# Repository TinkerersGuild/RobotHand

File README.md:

# RobotHand
http://tinker.eccentrify.com/guild/projects/robot-hand/

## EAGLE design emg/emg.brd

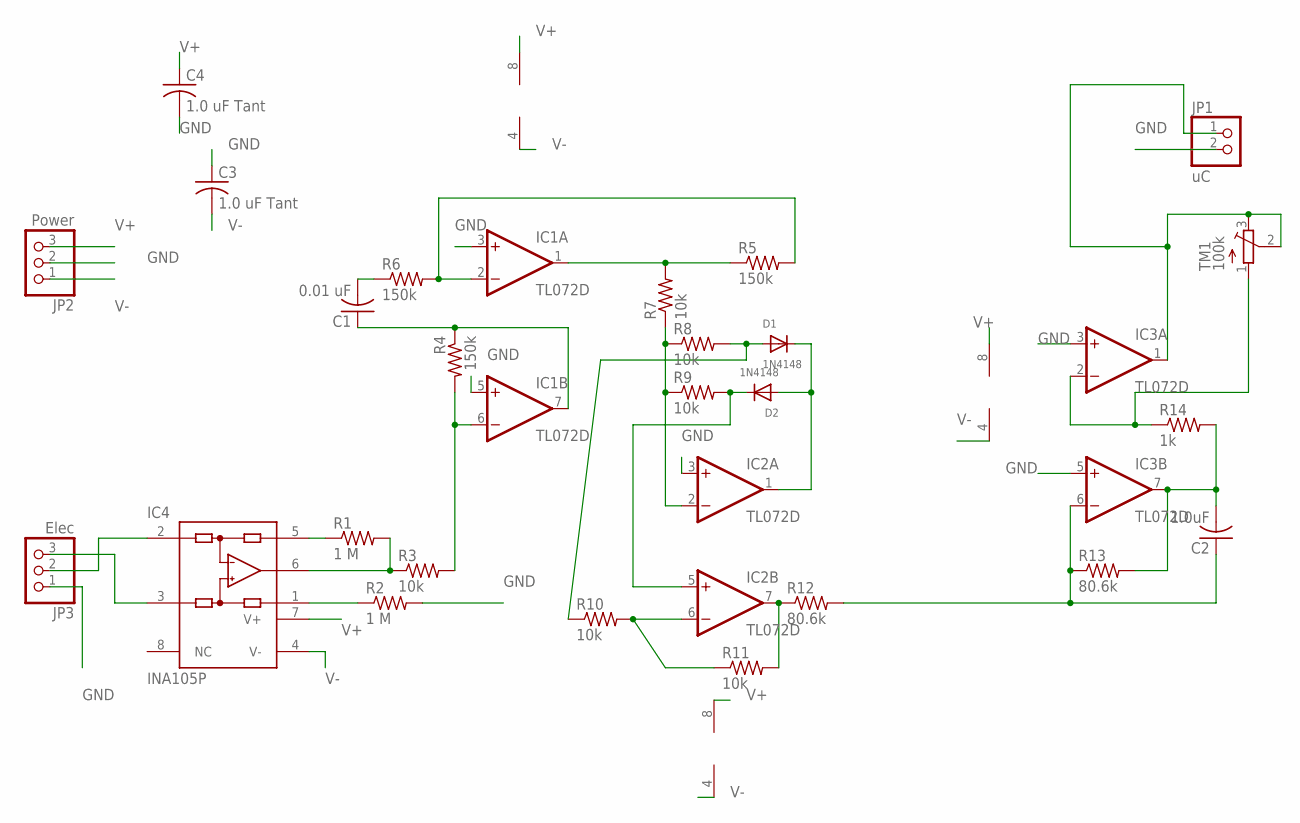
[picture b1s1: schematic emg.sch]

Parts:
C1: 0.01 uF; C0603
C2: 1.0uF; C0603
C3, C4: 1.0 uF Tant; C0805
D1, D2: 1N4148; DO-1N4148
IC1, IC2, IC3: TL072D; SO08
IC4: INA105P; DIL08
JP1: uC; 1X02
JP2: Power; 1X03
JP3: Elec; 1X03
R1, R2: 1 M; R0603
R3, R7, R8, R9, R10, R11: 10k; R0603
R4, R5, R6: 150k; R0603
R12, R13: 80.6k; R1206
R14: 1k; R0603
TM1: 100k; TC33X

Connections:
11: IC1.6 (-IN), R3.2, R4.2
23: IC1.2 (-IN), R5.2, R6.2
GND: C3.1, C4.2, IC1.3 (+IN), IC1.5 (+IN), IC2.3 (+IN), IC3.3 (+IN), IC3.5 (+IN), JP1.2, JP2.2, JP3.1, R2.2
unnamed: IC4.5 (SENSE), R1.1
unnamed: IC4.1 (REF), R2.1
unnamed: IC4.6 (OUT), R1.2, R3.1
unnamed: C1.1, IC1.7 (OUT), R4.1
unnamed: IC3.2 (-IN), R14.1, TM1.1 (A)
unnamed: D1.A, R8.2, R10.1
unnamed: IC1.1 (OUT), R5.1, R7.2
unnamed: D2.C, IC2.5 (+IN), R9.2
unnamed: C1.2, R6.1
unnamed: D1.C, D2.A, IC2.1 (OUT)
unnamed: IC2.7 (OUT), R11.2, R12.1
unnamed: C2.2, IC3.7 (OUT), R13.2, R14.2
unnamed: IC4.2 (-IN), JP3.2
unnamed: IC3.1 (OUT), JP1.1, TM1.2 (S), TM1.3 (E)
unnamed: IC4.3 (+IN), JP3.3
unnamed: IC2.6 (-IN), R10.2, R11.1
O1: C2.1, IC3.6 (-IN), R12.2, R13.1
P2: IC2.2 (-IN), R7.1, R8.1, R9.1
V+: C4.1, IC1.8 (V+), IC2.8 (V+), IC3.8 (V+), IC4.7 (V+), JP2.3
V-: C3.2, IC1.4 (V-), IC2.4 (V-), IC3.4 (V-), IC4.4 (V-), JP2.1

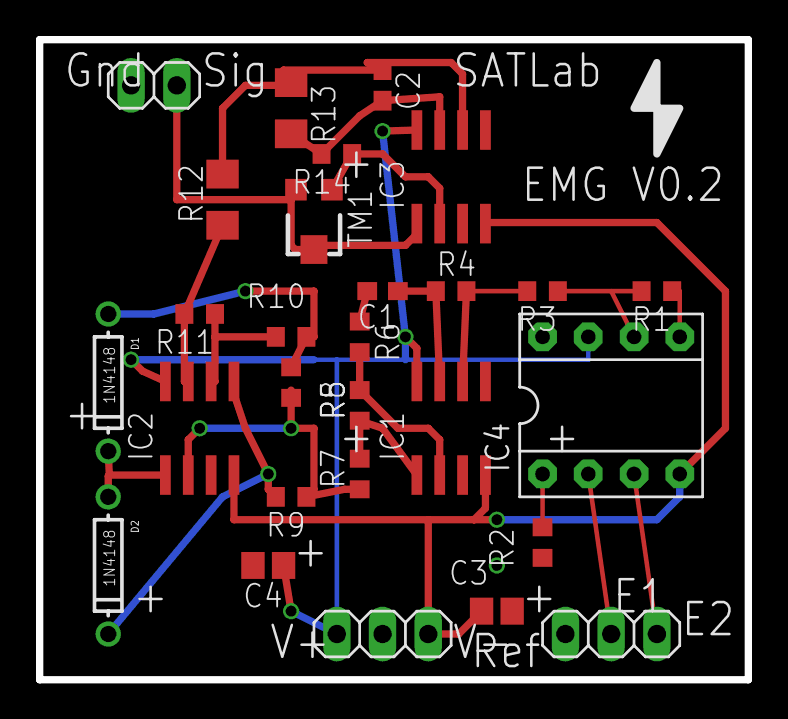
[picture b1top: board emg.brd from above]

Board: 2 copper layers, 39.4 x 35.6 mm, 28 parts (0 on the bottom side), 23 nets.

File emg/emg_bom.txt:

Partlist exported from /home/solitaire/eagle/emg/emg.sch at 3/12/15 11:13 PM

Qty Value       Device         Package   Parts                    Description                                 MF                MPN      OC_FARNELL OC_NEWARK
1   0.01 uF     C-USC0603      C0603     C1                       CAPACITOR, American symbol                                                                 
2   1 M         R-US_R0603     R0603     R1, R2                   RESISTOR, American symbol                                                                  
2   1.0 uF Tant C-USC0805      C0805     C3, C4                   CAPACITOR, American symbol                                                                 
1   1.0uF       C-USC0603      C0603     C2                       CAPACITOR, American symbol                                                                 
1   100k        TRIMPOTTC33X   TC33X     TM1                      SMT trimmer potentiometer part number TC33X                                                
6   10k         R-US_R0603     R0603     R3, R7, R8, R9, R10, R11 RESISTOR, American symbol                                                                  
3   150k        R-US_R0603     R0603     R4, R5, R6               RESISTOR, American symbol                                                                  
2   1N4148      DIODEDO-1N4148 DO-1N4148 D1, D2                   Diode                                                                                      
1   1k          R-US_R0603     R0603     R14                      RESISTOR, American symbol                                                                  
2   80.6k       R-US_R0603     R0603     R12, R13                 RESISTOR, American symbol                                                                  
1   Elec        PINHD-1X3      1X03      JP3                      PIN HEADER                                                                                 
1   INA105P     INA105P        DIL08     IC4                      Precision Unity Gain Diff. Amplifier        TEXAS INSTRUMENTS INA105KP 1651850    04M4538  
1   Power       PINHD-1X3      1X03      JP2                      PIN HEADER                                                                                 
3   TL072D      TL072D         SO08      IC1, IC2, IC3            OP AMP                                                                                     
1   uC          PINHD-1X2      1X02      JP1                      PIN HEADER

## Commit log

2017-06-22 EMG board design files for Eagle
2017-06-22 Add emg directory for emg schematics and board files
